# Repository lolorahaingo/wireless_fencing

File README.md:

# Wireless Fencing

> Replacing the wired scoring apparatus in competitive fencing with a fully wireless system built on Raspberry Pi Pico W microcontrollers.

---

## The Problem

In competitive foil fencing, every touch is detected by an electronic scoring apparatus connected to both fencers through **15-meter retractable cables**. These cables restrict movement, require constant maintenance, and make the sport inaccessible outside of dedicated venues.

**The fundamental challenge of going wireless:** without a physical wire connecting both fencers, there is **no common electrical ground** between them. The traditional system relies on DC circuits that require this shared reference. A completely different detection approach is needed.

---

## The Solution

Each fencer wears a **Raspberry Pi Pico W** that generates unique **AC square wave frequencies** on their conductive surfaces (lame/cuirasse). When a fencer's foil tip touches the opponent's valid target, the frequency is detected through the foil's internal wiring and identified — all without any electrical connection between the two fencers.

```
                    ┌─────────────────────────────────────────────────────────┐
                    │                    NO WIRE BETWEEN FENCERS              │
                    │                                                         │
  FENCER A          │          WiFi UDP            │          FENCER B        │
 ┌──────────┐       │       ┌──────────┐           │       ┌──────────┐      │
 │ Pico W   │       │       │ CENTRAL  │           │       │ Pico W   │      │
 │          │  ─ ─ ─│─ ─ ─ >│ Pico W   │< ─ ─ ─ ─ │─ ─ ─  │          │      │
 │ Generates│       │       │          │           │       │ Generates│      │
 │ Freq A   │       │       │ Arbitrate│           │       │ Freq B   │      │
 │ on lame  │       │       │ & Score  │           │       │ on lame  │      │
 └────┬─────┘       │       └──────────┘           │       └────┬─────┘      │
      │             │                                           │            │
   ┌──┴──┐          │                                        ┌──┴──┐         │
   │LAME │ ← Freq A │    Foil tip touches lame →             │LAME │ ← Freq B
   │     │          │    Freq detected = VALID TOUCH          │     │         │
   └─────┘          │                                        └─────┘         │
                    └─────────────────────────────────────────────────────────┘
```

### Why This Works

AC signals can traverse a single wire between two independently powered boards through **parasitic capacitive coupling** — the stray capacitance between the fencer's body, the floor, and the environment acts as the return path. This was the core hypothesis of the project, and it has been **experimentally validated**.

---

## System Architecture

### Per-Fencer Electronics

Each Pico W interfaces with the standard **3-wire body cord** (FIE convention) through a custom circuit with MOSFET buffers:

```
                         PICO W (RP2040)
                    ┌─────────────────────┐
                    │                     │
    ┌───────────────┤ GP14 (PWM out)      │
    │               │                     │
    │  ┌────────────┤ GP2  (interrupt in) │
    │  │            │                     │
    │  │  ┌─────────┤ GP16 (digital in)   │
    │  │  │         │                     │
    │  │  │         │ GP17 (PWM out)  ────┼──┐  (Mode Time-Division)
    │  │  │         │ GP15 (digital out)──┼──┤  (Mode Time-Division)
    │  │  │         └─────────────────────┘  │
    │  │  │                                  │
    ▼  ▼  ▼                                  ▼
 ┌──────────────────────────────────────────────┐
 │              MOSFET BUFFER STAGE              │
 │                                               │
 │   VBUS (5V)          VBUS (5V)                │
 │      │                  │                     │
 │   [100R]             [MOSFET C] ← GP15       │
 │      │                  │                     │
 │      ├─── Line A       [100R]                 │
 │      │   (red)          │                     │
 │   [MOSFET A]            ├─── Line C           │
 │      │    ← GP14        │   (green)           │
 │     GND              [MOSFET B] ← GP17       │
 │                         │                     │
 │                        GND                    │
 │                                               │
 │   GP2 ──┬── Line B (blue)                    │
 │         │                                     │
 │      [10kR] pull-down                        │
 │         │                                     │
 │        GND                                    │
 └───────────────────────────────────────────────┘
          │         │         │
          ▼         ▼         ▼
     ┌─────────────────────────────┐
     │       BODY CORD (3 wires)   │
     │                             │
     │  Line A ──── Lame/Cuirasse  │  ← emits Freq_VALID
     │  Line B ──── Foil tip       │  ← detects frequency
     │  Line C ──── Guard/shell    │  ← button detection (DC)
     └─────────────────────────────┘
```

### Detection Logic

The foil's push-button (German tip) is **normally closed**, connecting lines B and C. When the fencer presses the tip against a target, the circuit opens:

```
 BUTTON STATE          ELECTRICAL PATH              RESULT
 ─────────────────────────────────────────────────────────────
 Not pressed      B ←→ C connected (closed)     Nothing (no touch)
 (rest)           GP16 reads LOW (pulled down
                  by GP2's 10kΩ via B→C path)

 Pressed +        B isolated, tip touches        VALID TOUCH
 tip on lame      opponent's lame → Freq_VALID   (colored light)
                  detected on GP2

 Pressed +        B isolated, tip touches        No light
 tip on guard     neutral surface → Freq_NEUTRE  (annulled)

 Pressed +        B isolated, tip in air         WHITE LIGHT
 tip in air       no frequency on GP2            (off-target)
 ─────────────────────────────────────────────────────────────
```

### Communication

```
  Fencer A                                    Fencer B
  Pico W ──── WiFi UDP ────┐  ┌──── WiFi UDP ──── Pico W
                            ▼  ▼
                      ┌──────────┐
                      │ CENTRAL  │
                      │ Pico W   │
                      │          │
                      │ • AP mode│
                      │ • Lockout│  300-350ms (FIE rules)
                      │ • Dwell  │  15ms minimum contact
                      │ • Score  │
                      │ • LEDs   │
                      └──────────┘
```

- **Protocol:** Raw UDP over WiFi (ESP-NOW is Espressif-only, incompatible with Pico W's CYW43439 chip)
- **Topology:** Central Pico W acts as WiFi Access Point
- **Target latency:** < 20ms (well within the 300ms lockout window)

---

## Engineering Journey

This project follows a rigorous **hypothesis-driven** approach: each phase validates a specific assumption before building on it. Several discoveries forced significant architecture redesigns.

### Phase 0 — Proof of Concept

| Phase | Test | Result |
|-------|------|--------|
| 0.1 | Frequency detection on same board (Arduino Mega) | 25 kHz detected via interrupt counting |
| 0.2 | Multi-frequency classification (20/25/40 kHz) | 3 frequencies distinguished with ±2 kHz tolerance |
| 0.3 | **Detection without common ground** (Mega → Pico W) | ~19 kHz detected through parasitic coupling |
| 0.4 | Pico-to-Pico without common ground | **20,020 Hz** — near-perfect with 10kΩ pull-down |

> **Key validation:** AC signals traverse a single wire between independently powered boards. The core hypothesis holds.

### Phase 1 — Real Equipment Integration

This is where the real engineering challenges emerged:

#### Challenge 1: Capacitive Load of the Lame

The conductive lame (target vest) forms a large parasitic capacitor with the environment. The Pico's GPIO (3.3V, 12mA) couldn't drive it at 20 kHz.

```
 Problem:  GPIO direct → lame         5-7 kHz (should be 20 kHz)
 Solution: MOSFET 2N7000 buffer       20 kHz perfect
           + 100Ω pull-up to 5V
           (10kΩ pull-up was too weak — only 0.5mA couldn't charge
            the parasitic capacitance fast enough)
```

#### Challenge 2: Parasitic B↔C Coupling Inside the Foil

Lines B and C run millimeters apart inside the blade groove, forming a parasitic capacitor. The 5V/50mA buffered signal on line C leaked to line B, making it impossible to emit on C and detect on B simultaneously.

```
 Before (4-pin design):
   GP14 → emit on A (lame)     ✓
   GP2  ← detect on B (tip)    ✗ sees C's signal via parasitic coupling
   GP16 → emit on C (guard)    ✗ leaks to B
   GP17 ← detect button        ✗ always sees 20 kHz

 After (3-pin redesign):
   GP14 → emit on A (lame)     ✓ MOSFET buffer
   GP2  ← detect on B (tip)    ✓ clean signal, no C emission
   GP16 ← detect button (DC)   ✓ exploits DC vs AC difference
```

> **Insight:** Capacitive coupling blocks DC but passes AC. The mechanical button passes DC but the parasitic coupling doesn't. By reading DC on line C, we can detect the button state without any interference.

#### Challenge 3: 5V Signal Crashing the Pico

When the foil tip touches the lame (5V via MOSFET), the signal travels back through the button to GP16, exceeding the 3.3V GPIO tolerance and causing a latch-up reset.

```
 Solution: 10kΩ series resistor on GP16
           Limits current to 0.5mA (protection diodes handle it)
           Button reading still works: 0.47V (LOW) / 2.75V (HIGH)
```

#### Challenge 4: Signal Attenuation in the Foil

The foil's internal wire (~90cm in the blade groove) runs ~1mm from the metal blade, forming a **~10nF parasitic capacitor** that shunts AC signals to ground.

```
 Frequency    Impedance (10nF)    Detection
 ──────────────────────────────────────────
 20 kHz       ~800Ω               1,700 Hz detected (massive loss)
  5 kHz       ~3.2kΩ              500-1,700 Hz (still too much loss)
  1 kHz       ~16kΩ               should pass (to be validated)
```

> **Current blocker:** Frequencies must be lowered from 20-40 kHz to ~1-3 kHz. Experimental validation pending.

### Progress Overview

```
 Phase 0   Proof of Concept                          ██████████ DONE
 Phase 1   Real Equipment Integration                ████████░░ 80% (freq. validation pending)
 Phase 2   Complete System (Simple + Time-Division)  ░░░░░░░░░░ TODO
 Phase 3   WiFi UDP Communication                    ░░░░░░░░░░ TODO
 Phase 4   FIE Arbitration Logic                     ░░░░░░░░░░ TODO
 Phase 5   Full 2-Fencer Integration                 ░░░░░░░░░░ TODO
 Phase 6   Polish (LEDs, battery, enclosure)         ░░░░░░░░░░ TODO
```

---

## Key Technical Decisions

| Decision | Choice | Why |
|----------|--------|-----|
| **Detection method** | Interrupt pulse counting (not Goertzel/FFT) | Signal is square wave — energy spread across harmonics makes FFT unreliable. Counting rising edges is simpler and more robust |
| **Signal generation** | RP2040 hardware PWM (not `tone()`) | `tone()` on Pico W is imprecise at high frequencies (~14 kHz instead of 20 kHz). Hardware PWM is cycle-exact |
| **Communication** | WiFi UDP (not ESP-NOW) | ESP-NOW is Espressif-only. Pico W uses Infineon CYW43439 — must use standard WiFi |
| **Button detection** | DC reading on line C (not RC filter) | RC filter approach failed due to B↔C parasitic coupling. DC reading exploits the physical difference between capacitive coupling (blocks DC) and mechanical switch (passes DC) |
| **Current buffer** | 2N7000 MOSFET + 100Ω pull-up to 5V | GPIO can't drive capacitive loads. 100Ω provides ~50mA — enough to charge/discharge parasitic capacitance at 20 kHz |
| **Receiver pull-down** | External 10kΩ (not internal ~50kΩ) | Internal pull-down too weak for 3.3V signals without common ground. 10kΩ gives perfect detection |

---

## Hardware

| Component | Role | Qty |
|-----------|------|-----|
| Raspberry Pi Pico W | Fencer controller + central arbiter | 3 |
| 2N7000 N-MOSFET | Current buffer for driving conductive surfaces | 3 per fencer |
| 100Ω resistors | MOSFET pull-ups + gate protection | 4 per fencer |
| 10kΩ resistors | Receiver pull-down + GP16 protection | 2 per fencer |
| Electric foil (German tip) | Standard FIE weapon | 2 |
| Body cord (3-wire) | Standard FIE body cord | 2 |
| Conductive lame | Valid target surface | 2 |

A custom PCB is being designed in **KiCad 9** (`wireless_fencing_fencer/`).

---

## Project Structure

```
wireless_fencing/
├── phase0_1_freq_interrupt/     # Frequency detection on Arduino Mega
├── phase0_2_freq_detection/     # Multi-frequency classification
├── phase0_3_no_common_gnd/      # No-common-ground validation
│   ├── mega_generator/          #   Arduino Mega signal generator
│   └── pico_receiver/           #   Pico W receiver
├── phase0_4_pico_to_pico/       # Pico-to-Pico validation
│   ├── pico_generator/          #   PWM hardware generator
│   └── pico_receiver/           #   Interrupt-based receiver
├── phase1_5_button_detect/      # Button detection (RC approach — abandoned)
├── phase1_6_button_dc/          # Button detection via DC + diagnostic tests
├── wireless_fencing_fencer/     # KiCad 9 PCB design
├── gpio_test/                   # GPIO validation utilities
├── PROJECT_PLAN.md              # Detailed engineering log (1000+ lines)
└── CLAUDE.md                    # AI assistant context file
```

---

## FIE Compliance

The system targets compliance with FIE (International Fencing Federation) timing specifications for foil:

| Parameter | FIE Specification | System Target |
|-----------|-------------------|---------------|
| Dwell time (minimum contact) | 15ms ± 0.5ms | Measured per touch |
| Lockout time | 300-350ms | Configurable timer on central |
| Communication latency | — | < 20ms (UDP) |

---

## Tech Stack

- **Microcontroller:** Raspberry Pi Pico W (RP2040, Cortex-M0+, 133 MHz)
- **Framework:** Arduino (earlephilhower core)
- **Build system:** PlatformIO
- **Signal generation:** RP2040 hardware PWM (`hardware/pwm.h`)
- **PCB design:** KiCad 9
- **Communication:** WiFi UDP (CYW43439)

---

<p align="center">
  <i>An ongoing R&D project exploring the intersection of embedded systems, signal processing, and competitive sports.</i>
</p>

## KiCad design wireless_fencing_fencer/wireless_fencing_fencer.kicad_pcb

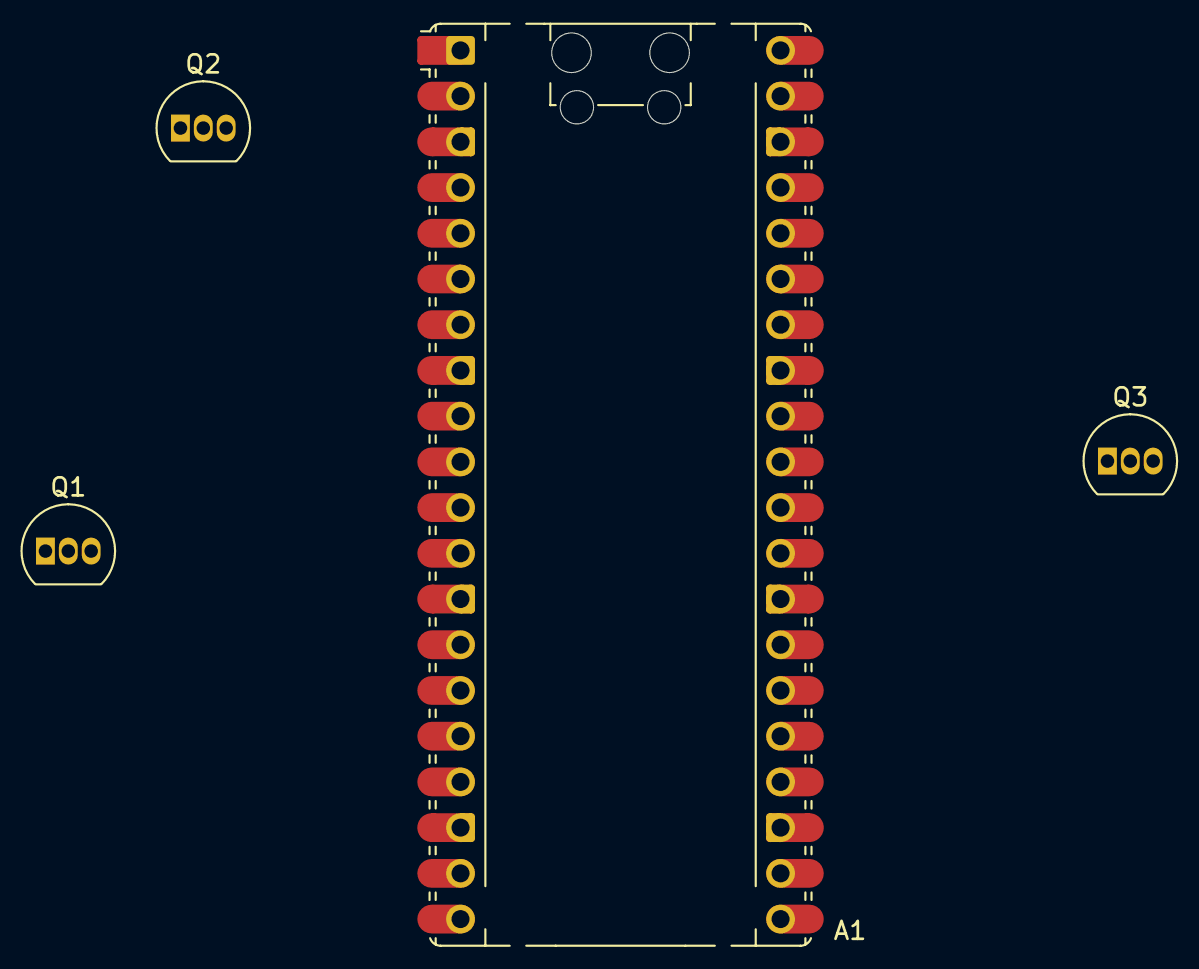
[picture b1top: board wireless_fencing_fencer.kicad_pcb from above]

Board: 2 copper layers, 4 parts (0 on the bottom side), 2 nets, no tracks yet.

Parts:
A1: RaspberryPi_Pico; RaspberryPi_Pico_Common_Unspecified
Q1, Q2, Q3: 2N7000; TO-92_Inline

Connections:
GND: A1.3 (GND), A1.8 (GND), A1.13 (GND), A1.18 (GND), A1.23 (GND), A1.28 (GND), A1.38 (GND)
unnamed: A1.14 (GPIO10), Q1.2 (G)

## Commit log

2026-02-18 Initial commit: project plan for wireless fencing scoring system
    Document the full architecture for a wireless foil fencing scoring system
    using Raspberry Pi Pico 2W with frequency-based touch detection to replace
    the common ground of wired systems.
2026-02-19 Phase 0.1-0.3: validate frequency detection without common GND
    - Add phase0_1 (interrupt-based freq detection on Mega, same board)
    - Add phase0_2 (multi-frequency classification on Mega, same board)
    - Add phase0_3 (Mega generator + Pico W receiver, no common GND)
    - Key result: signal detection works across isolated power supplies
    (Mega on mains adapter, Pico W on Mac battery via USB)
    - Update PROJECT_PLAN.md with all findings:
2026-02-19 Phase 0.4: validate Pico-to-Pico detection with 10kΩ pull-down
    - Add phase0_4 Pico W generator (PWM hardware, not tone()) and receiver
    - Key findings:
    - tone() is inaccurate on Pico W at high frequencies (~14-16 kHz vs 20 kHz)
    - PWM hardware (hardware/pwm.h) generates exact frequencies
    - Without pull-down: only ~80% of rising edges detected (~16 kHz read)
    - Internal pull-down (50kΩ): insufficient
2026-02-24 Phase 1: document cuirasse capacitive load problem and buffer solution
    Tests with body wire + cuirasse reveal GPIO cannot drive the capacitive
    load at 20 kHz (5-7 kHz detected on chair, 10-19 kHz in air vs 20 kHz
    on direct wire). Root cause: parasitic capacitance of the large conductive
    surface. Solution: MOSFET buffer (2N7000) between GPIO and cuirasse,
    powered by VBUS 5V. Awaiting components to validate.
2026-02-25 Phase 1: validate MOSFET 2N7000 buffer with 100Ω pull-up for cuirasse
    Buffer circuit (2N7000 + 100Ω pull-up to VBUS 5V) resolves capacitive
    load problem on cuirasse. 20 kHz detected reliably through body wire +
    foil touching cuirasse on chair. 10kΩ pull-up was too weak (only 20-50 Hz
    on drain). Signal detected even with button unpressed — expected behavior,
    requires dedicated GPIO for button state detection (GP20).
2026-02-25 Phase 1.5: discover B↔C parasitic coupling, revise architecture to 3-pin design
    Test with RC filter on GP16 revealed that the MOSFET buffer signal on
    line C (20kHz, 5V/50mA) bleeds into line B through capacitive coupling
    inside the foil. GP2 sees ~20kHz permanently regardless of button state.
    RC filter approach abandoned. Architecture revised from 4 pins to 3 pins:
    - GP14 (PWM) → line A → Freq_VALID on cuirasse (via MOSFET buffer)
    - GP2 (GPIO IN + 10kΩ pull-down) → line B → frequency detection
2026-02-26 Update architecture: complete circuit with 3 MOSFETs, add GP15, rename to Mode Simple / Mode Time-Division
    - Add GP15 (MOSFET C) to cut pull-up power during button detection phase
    - Full circuit: GP14→MOSFET A (line A), GP17→MOSFET B + GP15→MOSFET C (line C), GP16 (button read), GP2 (freq detect)
    - Circuit is wired once; switching Mode Simple → Mode Time-Division is software only
    - In Mode Simple: GP15=LOW, GP17=LOW (emission circuit inactive)
    - In Mode Time-Division: GP15+GP17 control 9ms emit / 1ms detect cycle
    - Rename Option 2 → Mode Simple, Option 3 → Mode Time-Division
2026-02-27 Phase 1.6-1.7: button DC validated, GP16 crash fixed, foil attenuation discovered — frequencies must be lowered to 1-3 kHz
    - Phase 1.6 DONE: button detection via DC on GP16 works reliably
    - Phase 1.7 partial: GP16 5V crash fixed (10kΩ series resistor),
    interrupt avalanche fixed (attach/detach by button state),
    foil internal wire attenuation discovered (BLOCKING)
    - Foil parasitic capacitance (~10nF) shunts AC signal to blade:
    20kHz → only ~1700 Hz detected, frequencies must drop to 1-3 kHz
2026-03-02 Add README: recruiter-friendly project overview with architecture diagrams and engineering journey
